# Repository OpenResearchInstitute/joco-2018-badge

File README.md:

# joco-2018-badge

Code and documentation for the unofficial electronic badge for the JoCo Cruise 2018.

This is based on the excellent work that the AND!XOR team produced for the DEFCON 25 Bender Badge.

All code and hardware design files are closed until Feb 26th, 2018 and then are licensed under the Apache license 2.0 unless superceded by notices in individual files or directories.

## Getting Started

Some resources must be installed outside of this source tree. One of these is the Nordic SDK.

Choose a place to install these on your file system. For example, we'll use "/src/joco-support/".

Download the version 12.3 of the Nordic SDK [from here](https://developer.nordicsemi.com/nRF5_SDK/nRF5_SDK_v12.x.x/nRF5_SDK_12.3.0_d7731ad.zip) and unzip it into the directory you chose.

It's known that later versions of the SDK are not compatible with the existing badge code. We may work on fixing that, which is why we don't install the SDK in the source tree for the project.

Now edit your shell init or rc file to set the following environment variable when you create a shell, substituting your chosen path:

```
export SDK_ROOT=/src/joco-support/nRF5_SDK_12.3.0_d7731ad
```

### Ubuntu Installation (non-ARM host)

Download the GNU ARM Embedded Toolchain. Choose one of these methods:

* Download the latest from <https://developer.arm.com/open-source/gnu-toolchain/gnu-rm/downloads> and unpack it into its own directory in `/usr/local`. Or,

* Download the version that Nordic used to test their SDK, 4.9 2015q3, from <https://launchpad.net/gcc-arm-embedded/+milestone/4.9-2015-q3-update> and unpack it into its own directory in `/usr/local`. Or,

* `sudo apt-get install gcc-arm-none-eabi` and take your chances on whatever version is current for your Linux. This may be your only option if you're running Linux on a non-x86 platform.

Then edit `$SDK_ROOT/components/toolchain/gcc/Makefile.posix` and change the value for `GNU_INSTALL_ROOT` to the directory where your toolchain was installed.

If you plan to hook up hardware for programming and debugging, you'll need the Segger JLink software. It's available from <https://www.segger.com/downloads/jlink/> for a variety of host platforms. We used version V6.18b, but the latest version is probably fine. To install on Ubuntu on an Intel PC:

`sudo dpkg -i <path-to-downloads>/JLink_Linux_V618b_x86_64.deb`

You'll also need a couple of command line tools from Nordic. These are available from <http://infocenter.nordicsemi.com/topic/com.nordic.infocenter.tools/dita/tools/nrf5x_command_line_tools/nrf5x_installation.html?cp=5_1_1>. We used version 9.7.0, but the latest version is probably fine. Install them in a location outside this project, like the Nordic SDK. For example using the location "/src/joco-support", you can do the following:

```
mkdir -p /src/joco-support/bin
cd /src/joco-support/bin
tar xvf <path-to-downloads>/nRF5x-Command-Line-Tools_9_7_0_Linux-x86_64.tar
```

Now edit your shell init or rc file to set the following environment variable when you create a shell, substituting your chosen path:

```
export NRFJ_BIN=/src/joco-support/bin
```

#### Ubuntu on an ARM Host

If you want to develop on an ARM-based host, most of the components are available.

The Nordic SDK is the same.

You should be able to `sudo apt-get install gcc-arm-none-eabi` to get the toolchain.

You can get JLink software [from Segger here](https://www.segger.com/downloads/jlink/#J-LinkSoftwareAndDocumentationPack)

The command line tools nrfjprog and mergehex are not currently available for ARM hosts. You can use the JLink tools to program the device, so you can probably work around nrfjprog.

### Build the code

`cd firmware/manbearpig`

`make`

`cd ..`

`./update.sh`

### JTAG interface hardware

To flash the code to the badge and use the Ozone debugger, you'll need a JTAG hardware interface.
The one that was used by the development team is the Segger [J-Link EDU Mini](https://www.segger.com/products/debug-probes/j-link/models/j-link-edu-mini/).

It's much easier to connect to the board if you use a short flat cable and a mating header on the board end. All these can be purchased from these retailers:

* [J-Link EDU Min from Adafruit](https://www.adafruit.com/product/3571)
* [Ten pin JTAG cable from Adafruit](https://www.adafruit.com/product/1675) (not the same as the one that comes with the debugger)
* [Header from Mouser](https://www.mouser.com/ProductDetail/Harwin/M50-3500542?qs=9fQaSFfsqsyXI0P9tFOVoQ%3D%3D)

### Flashing the target

Two ways, either:

`cd firmware`

`./provision.sh`

or

`cd firmware/manbearpig`

`make flash_softdevice`

`make flash`

The `make flash_softdevice` can be omitted after the first time.

### Setting up the Segger Ozone debugger

This was correct for Ubuntu 14.04.5 64 bit

Install the Ozone package [from here](https://www.segger.com/downloads/jlink/#Ozone)

The manual is useful (same link)

IMPORTANT NOTE: 

Ozone version 2.56 would not work for me. It would halt execution in seemingly random places and not load source code.

Version 2.54b works fine

If you're using the Segger edu device, Select the device as Nordic nRF52832_xxAA

Choose SWD for the debugger device and NOT USB.

open the badge .out file to bring in source files

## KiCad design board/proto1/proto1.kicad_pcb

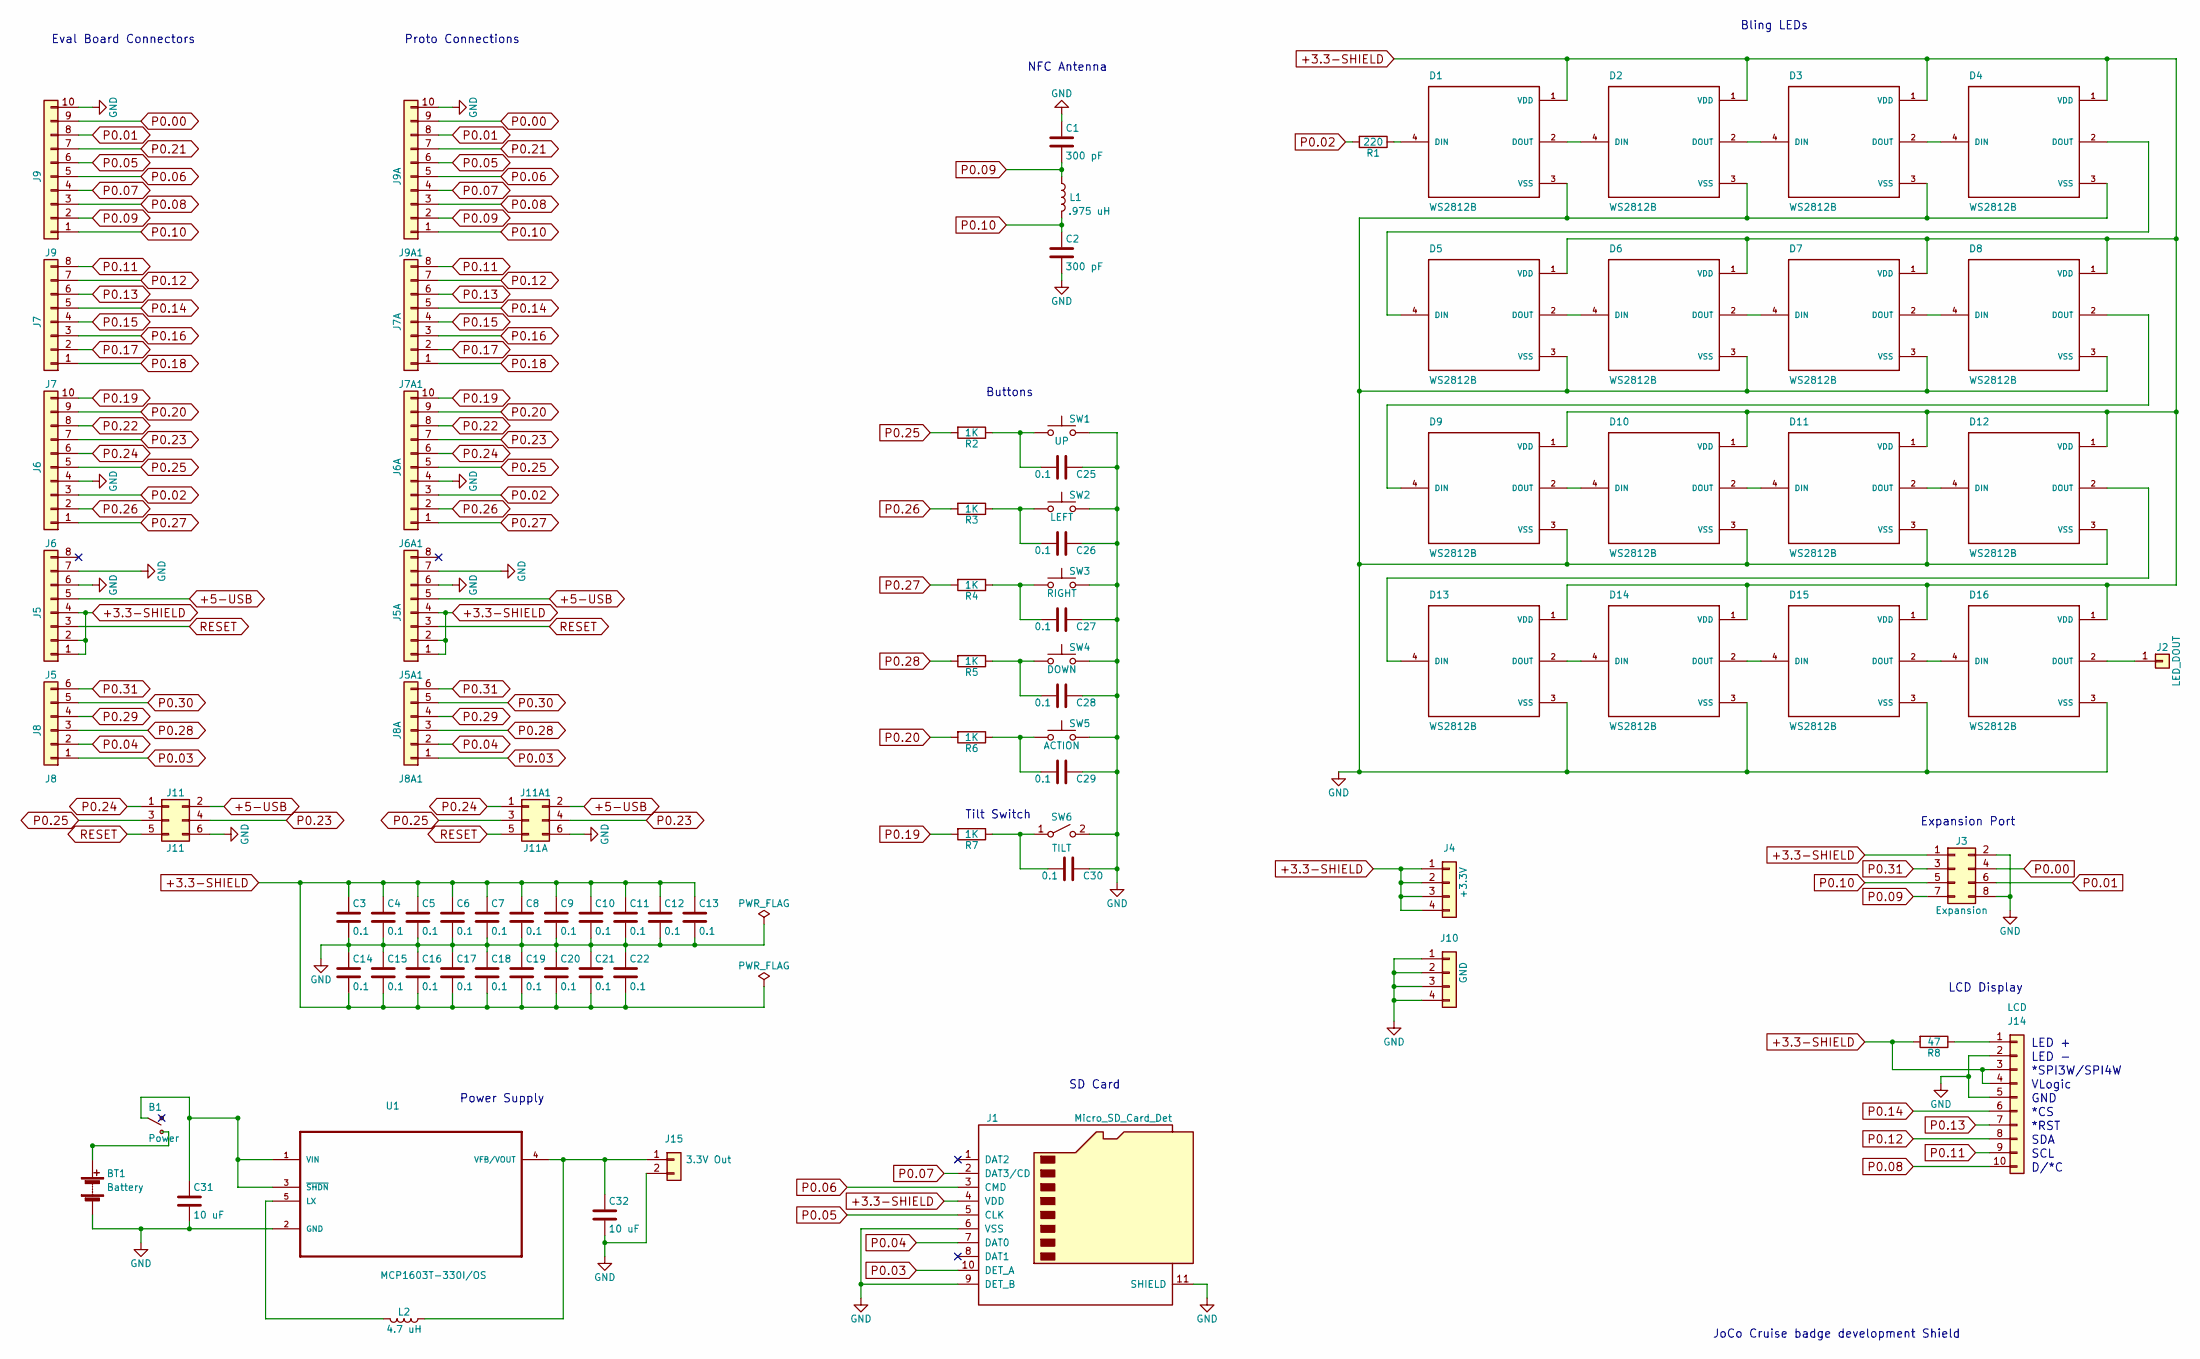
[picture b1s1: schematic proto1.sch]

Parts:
B1: Power; SSSS810701
BT1: Battery; R_Axial_DIN0411_L9.9mm_D3.6mm_P12.70mm_Horizontal
C1, C2: 300 pF; C_0805
C3, C4, C5, C6, C7, C8, C9, C10, C11, C12, C13, C14, C15, C16, C17, C18, C19, C20, C21, C22, C25, C26, C27, C28, C29, C30: 0.1; C_0805
C31, C32: 10 uF; C_1206
D1, D2, D3, D4, D5, D6, D7, D8, D9, D10, D11, D12, D13, D14, D15, D16: WS2812B; LED_WS2812B
J1: Micro_SD_Card_Det; newsdcard
J2: LED_DOUT; Pin_Header_Straight_1x01_Pitch2.54mm
J3: Expansion; Pin_Header_Straight_2x04_Pitch2.54mm
J4: +3.3V; Pin_Header_Straight_1x04_Pitch2.54mm
J5: J5; Pin_Header_Straight_1x08_Pitch2.54mm
J5A1: J5A; Pin_Header_Straight_1x08_Pitch2.54mm
J6: J6; Pin_Header_Straight_1x10_Pitch2.54mm
J6A1: J6A; Pin_Header_Straight_1x10_Pitch2.54mm
J7: J7; Pin_Header_Straight_1x08_Pitch2.54mm
J7A1: J7A; Pin_Header_Straight_1x08_Pitch2.54mm
J8: J8; Pin_Header_Straight_1x06_Pitch2.54mm
J8A1: J8A; Pin_Header_Straight_1x06_Pitch2.54mm
J9: J9; Pin_Header_Straight_1x10_Pitch2.54mm
J9A1: J9A; Pin_Header_Straight_1x10_Pitch2.54mm
J10: GND; Pin_Header_Straight_1x04_Pitch2.54mm
J11: J11; Pin_Header_Straight_2x03_Pitch2.54mm
J11A1: J11A; Pin_Header_Straight_2x03_Pitch2.54mm
J14: LCD; ZIF-505110-1092
J15: 3.3V Out; Pin_Header_Straight_1x02_Pitch2.54mm
L1: .975 uH; nfc-test2
L2: 4.7 uH; MAMK2520
R1: 220; R_0805
R2, R3, R4, R5, R6, R7: 1K; R_0805
R8: 47; R_0805
SW1: UP; PTS810
SW2: LEFT; PTS810
SW3: RIGHT; PTS810
SW4: DOWN; PTS810
SW5: ACTION; PTS810
SW6: TILT; R_Axial_DIN0207_L6.3mm_D2.5mm_P15.24mm_Horizontal
U1: MCP1603T-330I/OS; SOT95P280X110-5N

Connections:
+3.3-SHIELD: C3.1, C4.1, C5.1, C6.1, C7.1, C8.1, C9.1, C10.1, C11.1, C12.1, C13.1, C14.2, C15.2, C16.2, C17.2, C18.2, C19.2, C20.2, C21.2, C22.2, D1.1 (VDD), D2.1 (VDD), D3.1 (VDD), D4.1 (VDD), D5.1 (VDD), D6.1 (VDD), D7.1 (VDD), D8.1 (VDD), D9.1 (VDD), D10.1 (VDD), D11.1 (VDD), D12.1 (VDD), D13.1 (VDD), D14.1 (VDD), D15.1 (VDD), D16.1 (VDD), J1.4 (VDD), J3.1, J4.1, J4.2, J4.3, J4.4, J5.1, J5.2, J5.4, J5A1.1, J5A1.2, J5A1.4, J14.3, J14.4, R8.2
+5-USB: J5.5, J5A1.5, J11.2, J11A1.2
GND: BT1.2 (-), C1.1, C2.2, C3.2, C4.2, C5.2, C6.2, C7.2, C8.2, C9.2, C10.2, C11.2, C12.2, C13.2, C14.1, C15.1, C16.1, C17.1, C18.1, C19.1, C20.1, C21.1, C22.1, C25.1, C26.1, C27.1, C28.1, C29.1, C30.1, C31.2, C32.2, D1.3 (VSS), D2.3 (VSS), D3.3 (VSS), D4.3 (VSS), D5.3 (VSS), D6.3 (VSS), D7.3 (VSS), D8.3 (VSS), D9.3 (VSS), D10.3 (VSS), D11.3 (VSS), D12.3 (VSS), D13.3 (VSS), D14.3 (VSS), D15.3 (VSS), D16.3 (VSS), J1.6 (VSS), J1.9 (DET_B), J1.11 (SHIELD), J3.2, J3.8, J5.6, J5.7, J5A1.6, J5A1.7, J6.4, J6A1.4, J9.10, J9A1.10, J10.1, J10.2, J10.3, J10.4, J11.6, J11A1.6, J14.2, J14.5, J15.2, SW1.2, SW2.2, SW3.2, SW4.2, SW5.2, SW6.2 (B), U1.2 (GND)
unnamed: B1.1 (B), BT1.1 (+)
unnamed: B1.2 (COM), C31.1, U1.1 (VIN), U1.3 (~SHDN)
unnamed: C25.2, R2.1, SW1.1
unnamed: C26.2, R3.1, SW2.1
unnamed: C27.2, R4.1, SW3.1
unnamed: C28.2, R5.1, SW4.1
unnamed: C29.2, R6.1, SW5.1
unnamed: C30.2, R7.1, SW6.1 (A)
unnamed: C32.1, J15.1, L2.1, U1.4 (VFB/VOUT)
unnamed: D1.2 (DOUT), D2.4 (DIN)
unnamed: D1.4 (DIN), R1.1
unnamed: D2.2 (DOUT), D3.4 (DIN)
unnamed: D3.2 (DOUT), D4.4 (DIN)
unnamed: D4.2 (DOUT), D5.4 (DIN)
unnamed: D5.2 (DOUT), D6.4 (DIN)
unnamed: D6.2 (DOUT), D7.4 (DIN)
unnamed: D7.2 (DOUT), D8.4 (DIN)
unnamed: D8.2 (DOUT), D9.4 (DIN)
unnamed: D10.2 (DOUT), D11.4 (DIN)
unnamed: D9.2 (DOUT), D10.4 (DIN)
unnamed: D11.2 (DOUT), D12.4 (DIN)
unnamed: D12.2 (DOUT), D13.4 (DIN)
unnamed: D13.2 (DOUT), D14.4 (DIN)
unnamed: D14.2 (DOUT), D15.4 (DIN)
unnamed: D15.2 (DOUT), D16.4 (DIN)
unnamed: D16.2 (DOUT), J2.1
unnamed: J14.1, R8.1
unnamed: L2.2, U1.5 (LX)
P0.00: J3.4, J9.9, J9A1.9
P0.01: J3.6, J9.8, J9A1.8
P0.02: J6.3, J6A1.3, R1.2
P0.03: J1.10 (DET_A), J8.1, J8A1.1
P0.04: J1.7 (DAT0), J8.2, J8A1.2
P0.05: J1.5 (CLK), J9.6, J9A1.6
P0.06: J1.3 (CMD), J9.5, J9A1.5
P0.07: J1.2 (DAT3/CD), J9.4, J9A1.4
P0.08: J9.3, J9A1.3, J14.10
P0.09: C1.2, J3.7, J9.2, J9A1.2, L1.1
P0.10: C2.1, J3.5, J9.1, J9A1.1, L1.2
P0.11: J7.8, J7A1.8, J14.9
P0.12: J7.7, J7A1.7, J14.8
P0.13: J7.6, J7A1.6, J14.7
P0.14: J7.5, J7A1.5, J14.6
P0.15: J7.4, J7A1.4
P0.16: J7.3, J7A1.3
P0.17: J7.2, J7A1.2
P0.18: J7.1, J7A1.1
P0.19: J6.10, J6A1.10, R7.2
P0.20: J6.9, J6A1.9, R6.2
P0.21: J9.7, J9A1.7
P0.22: J6.8, J6A1.8
P0.23: J6.7, J6A1.7, J11.4, J11A1.4
P0.24: J6.6, J6A1.6, J11.1, J11A1.1
P0.25: J6.5, J6A1.5, J11.3, J11A1.3, R2.2
P0.26: J6.2, J6A1.2, R3.2
P0.27: J6.1, J6A1.1, R4.2
P0.28: J8.3, J8A1.3, R5.2
P0.29: J8.4, J8A1.4
P0.30: J8.5, J8A1.5
P0.31: J3.3, J8.6, J8A1.6
RESET: J5.3, J5A1.3, J11.5, J11A1.5

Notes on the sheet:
Eval Board Connectors
Proto Connections
NFC Antenna
SD Card
Bling LEDs
Buttons
Power Supply
Tilt Switch
LED +
LED -
*SPI3W/SPI4W
VLogic
GND
*CS
*RST
SDA
SCL
D/*C
LCD Display
JoCo Cruise badge development Shield
Expansion Port

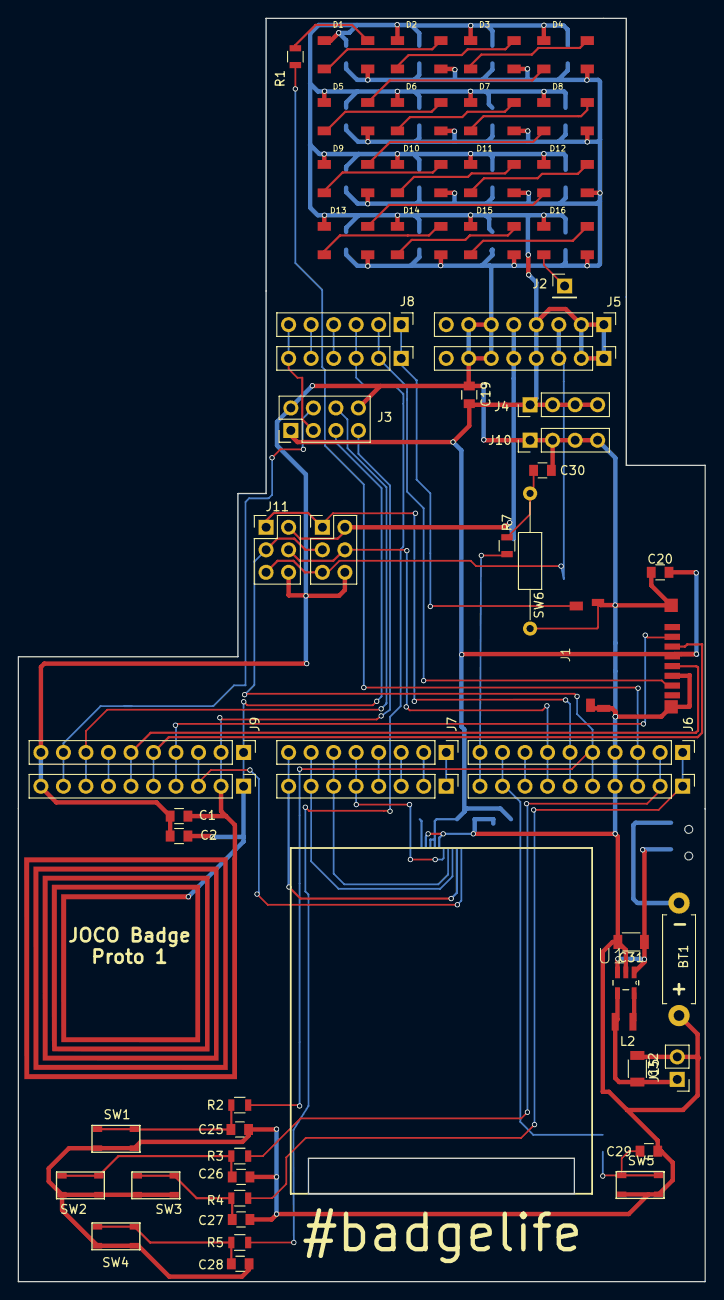
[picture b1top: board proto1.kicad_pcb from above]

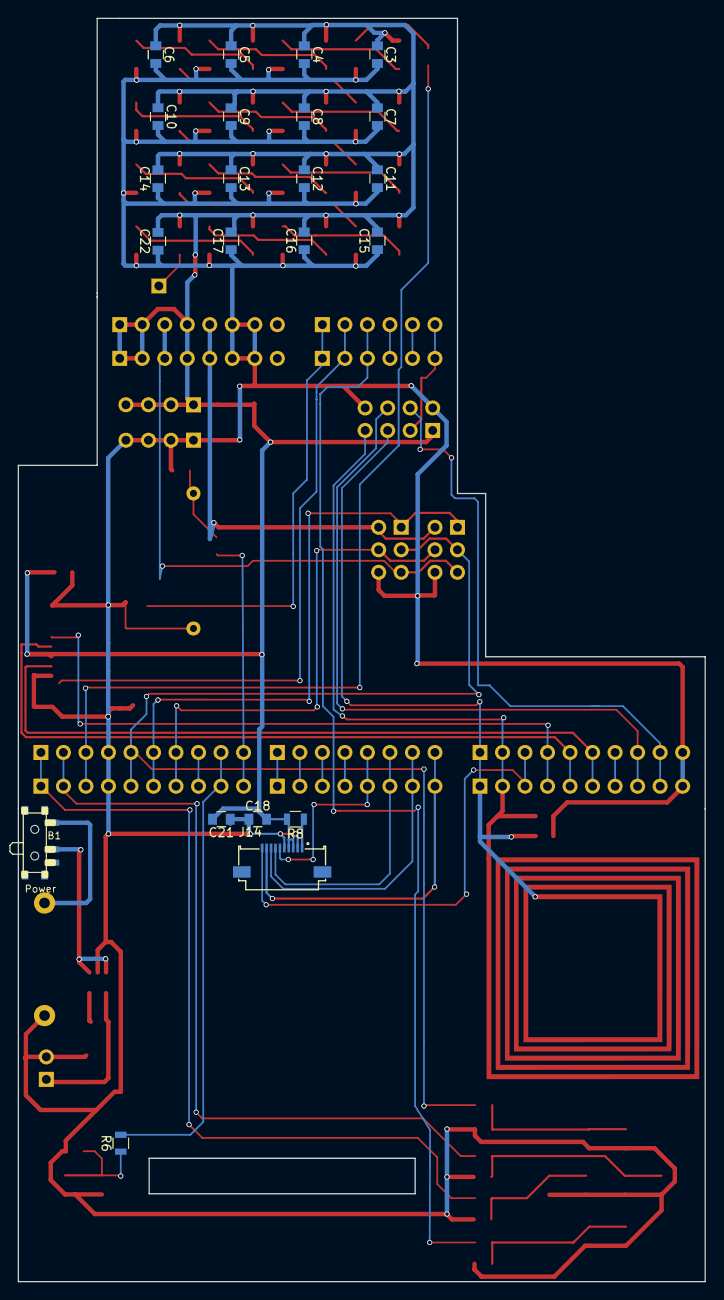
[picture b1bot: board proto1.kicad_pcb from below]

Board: 2 copper layers, 77.5 x 142.5 mm, 84 parts (22 on the bottom side), 64 nets.

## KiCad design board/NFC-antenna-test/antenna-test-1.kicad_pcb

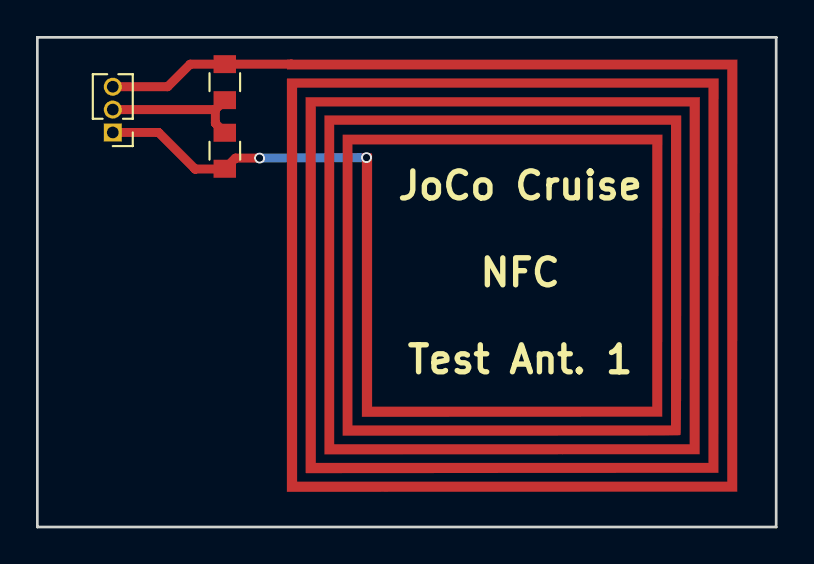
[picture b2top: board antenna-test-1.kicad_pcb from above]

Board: 2 copper layers, 41.0 x 27.2 mm, 4 parts (0 on the bottom side), 3 nets.

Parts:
C1, C2: C; C_0805
J1: ANT; Pin_Header_Straight_1x03_Pitch1.27mm
L1: L; nfc-test2

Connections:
GND: C1.1, C2.2, J1.2
unnamed: C1.2, J1.3, L1.1
unnamed: C2.1, J1.1, L1.2

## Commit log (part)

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2017-08-10 readme
2017-08-10 initial commit of ANDnXOR bender source
2017-08-14 Ignore a warning and clean up whitespace
    gcc is throwing a warning for using char as an array subscript even though the declaration is for uint8_t. So ignore that.
    Also, clean up lots of extra spaces and make tab use consistent
2017-08-20 Move spreadsheet to google docs, and update README
2017-08-27 Add first unfinished proto board designs
2017-08-31 more layout work
2017-08-31 unignore and add library files fro kicad
2017-09-04 lots more layout work
2017-09-05 Add rescue lib from version change
2017-09-05 Add cache.lib
2017-09-06 layout maybe finished
2017-09-12 Add final board info for proto1
2017-09-16 coverting files to Eagle, checking in data sheets
2017-09-16 added power suppy to proto2
2017-09-21 adding additional parts
2017-09-21 adding bling LEDs to proto2
2017-10-01 Remove Nordic SDK from the repo, add instructions.
    In order to make it cleaner to switch versions of the SDK,
    we no longer check the SDK into the repository.
    In order to make it easier to get started with the toolchain,
    there are now detailed instructions in README.md.
2017-10-01 Remove Nordic Command Line Tools from repo.
2017-10-01 Improve getting started instructions.
2017-10-04 Typo in SDK URL
2017-10-04 Improved Getting Started info
2017-10-06 strip out botnet code
2017-10-07 Move the SDK and platform-specific tools out of the repo
    Place the Nordic programming tools and SDK outside the git repository and use environment variables to point to them.
    This prevents having to maintain files in the local directory tree which aren't under git.
2017-10-11 Find Makefile.posix in the new location
2017-10-27 Change some defcon text to joco
2017-10-27 Make button repeat delay longer during code entry
2017-10-31 Add support for NFC
2017-11-12 adding outline of monkey to PCB
2017-11-12 silkscreen for monkey
2017-11-12 added gold teeth
2017-11-12 guides for LEDs, etc
2017-11-12 add guides for LEDs; place LEDs, battery, CPU
2017-11-12 adding original AI from Amy; board specifications (TBD)
2017-11-12 add .DS_Store to gitignore
2017-12-02 copy Amy's board revision to proto2 (change tPlace artwork)
2017-12-02 reduce LEDs to 14, add tilt switch, draw NFC antenna
2017-12-02 added expansion connector to schematic
2017-12-02 added programming cable connector
2017-12-02 add decoupling caps
2017-12-02 layout in process
2017-12-03 lots of routing going on
2017-12-03 routing almost done. I hate 2-layer PCBs
2017-12-03 goffing around with artwork
2017-12-03 change to SW-200D part
2017-12-03 remove unneeded pin labels
2017-12-04 added lanyard holes; thanks to AND\!XOR
2017-12-04 add earring holes
2017-12-05 changes for errors found by AI4QR
2017-12-16 remove Old backer bling code from firmware and files from SD card
2017-12-18 final changes to proto2, saving Gerbers
2017-12-27 Shuffle boot image and ANDNXOR backer bling
2017-12-27 change LED indices and function names for pirate monkey
2017-12-27 remove whiskey pirate clue for DC25 from the pirate bling
2017-12-27 Change various ANDnXOR menu headers and other things to JOCO2018
2017-12-28 Fix SD card omissions
2017-12-28 Fix some broken menus
2017-12-28 remove unused Bender archive from SD Card
2017-12-28 Fix LED bling for andnxor backer bling
2017-12-29 Change company ID for joco badge, update to handle interactions with bender
2017-12-29 increase menu delay to prevent double buttons
2017-12-29 Add image file tools
2017-12-29 Add Wil Wheaton bling mode
2017-12-29 Add pirate monkey boot intro image
2017-12-29 Add the readme from andnxor for the SD card
2018-01-01 move resistor out of way of display
2018-01-01 reset masks to 4mil
2018-01-01 add secret resistor
2018-01-07 remove andnxor reference and add a way to enable all bling modes easily
2018-01-07 Fix a typo in airplane mode
2018-01-07 Make tooth LED gold and flashing
2018-01-07 Change the background image for the menus to a pirate monkey one
2018-01-07 remove the ANDNXOR chip8 game
2018-01-08 move flex connector 1mm to the North
2018-01-08 move expansion connector
2018-01-08 move team and thanks position due to tild switch nove to back of board
2018-01-08 rotated SD card 180-degrees
2018-01-08 update assembly instructions for PCB
2018-01-09 change lanyard holes to 4mm
2018-01-10 WIP schematic rules
2018-01-10 change mask to blue for 5 boards
2018-01-10 swap out switch for one with better mechanical stability
2018-01-10 production board and Gerbers
2018-01-10 make note about hole in center of PCB
2018-01-20 Cropped GIFs for Bling
2018-01-20 Move new images to a new directory for source images
2018-01-20 Add more source image files
2018-01-20 Change yet anothe rbender string to joco, this time in ble
2018-01-21 Add code reading notes.
    These are notes I took while reading the AND!XOR Bender badge code,
    concentrating on particular subjects. They may or may not be useful
    for others trying to understand the code.
2018-01-21 Checked in DC25 Wall of Bender code to start Wall of Joco
2018-01-22 Add new bling modes
    Added new files to the SD card, bumped SD version
    Added new bling to the menu
    Deleted old files from SD card
2018-01-22 Resolve stack/heap crash in menu system
    Changed the menu system to cache only the icons that are visible
    on screen, instead of every icon for every menu entry. This relaxes
    the limit on how many menu items there can be, so specifically the
    custom bling menu can be much longer.
    Also installed the mechanism to control the sizes of the stack and
    the heap, in config/startup_config.h. However, the sizes currently
2018-01-26 Add for NFC payload
    Add actual content for the NFC tag emulation, consisting of a fixed text string.
2018-01-27 Update Wall of JoCo README for RTC.
2018-01-27 Update Wall of JoCo README, remove DEFCON
2018-01-27 Change the unlock constants and remap to bling for joco
    Edit the #define mask names to match what we're using them for in joco. Comment out some of the code that's used in beacon receiving to enable these, because we need to move it to be based on badge p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
2018-01-28 Add initial joco gameplay files
    Add new files and constants for game play. Add the score and last_level_dispensed to the state that gets saved.
2018-01-28 put some reasonable numbers in for RSSI
2018-01-28 Put the JoCo data we need in the BLE advertising data
    The 'level' field was repurposed to lld (last_level_dispensed)
    The 8 bit avatar field was replaces with a 16 bit score field.
    Data offsets were adjusted accordingly in the data.
    The new fields are read into the badge_db information for badges that are 'heard'
    This has not yet been tested to make sure it's sent and received correctly.
2018-01-29 Remove the rest of the badge activation code and tests
2018-01-29 change state encryption key
2018-01-30 Add code reading notes for connected mode.
2018-01-31 Merge trinket dispensing flag with score in BLE advertising
    It turns out that there was not enough room in the BLE data to add one more byte of data. By doing this, if the name is a full 8 bytes long, then it gets translated into a short naem format, and we d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
    The solution is to simply adevrtise a flag that incicates that the badge has some outstanding 'credits' for trinkets which can be dispensed. This flag is the high but of the 16 bit unsigned score val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
2018-02-01 Replace 6 calls to snprintf
    It seemed dumb to call snprintf 6 times to convert a byte array to Ascii hex, and the terminating numm that is created was wrong, so include a small function to do this task.
2018-02-01 Update BLE score on load from SD card
2018-02-01 Add basic BLE service for score and lld.
    Created a GATT service with two characteristics. One is a read-only
    struct containing the current score and last_level_dispensed. The
    other is a write-only 64-bit command code, which currently implements
    commands to set score and lld.
    Security: none yet. The read characteristic is completely public, and
    once that's spoofed it's easy to trick the station into sending you
2018-02-03 Added File Crypto Notes to codereading
2018-02-04 add db functions to store badges we've contacted/visited
2018-02-04 Make a copy to encrypt before encrypting!
2018-02-08 Crypto state and score cleanup
    Added macros in util_crypto.h to encapsulate some of the procedure for
    accessing the util_crypto routines. Changed mbp_state.c and score_ble.c
    to use them.
    Switched from separate score_set and lld_set functions to a single
    score_update function that does its own fetching of the data from the
    mbp_state database. Changed mbp_state.c to use it. The new update
2018-02-09 Add new visit tracking
    Completely rework the db/list of heard badges.
    Only joco badges that we haven't 'visited' are stored in
    the primary active list. Other badges and one's we've
    visited are stored in a second cache list, which is backed
    by the database on SD card for vistied badges.
2018-02-09 Change Scoring and joco hello bling
2018-02-10 Add a file to the DB directory so git keeps the directory
2018-02-11 Add name to NFC data
2018-02-11 Add a menu selection to view current game status
2018-02-11 Fix hello timing
    Hello timer was set using the non-local millis, and the next hello time
    was set to zero, which resulted in immediate hellos on boot before the
    splash screen even finished. Fixed this.
2018-02-11 Darker background image for joco hello bling
2018-02-11 remove some char cast warnings
2018-02-12 Add eye animation in idle mode
2018-02-13 Update NFC tag data on name change
2018-02-13 Truncate NFC data length to only used bytes
2018-02-13 Change icon for menu score entry and other improvements
    Also exit the score display on any button press.
    Bumped SD card and software version numbers.
2018-02-13 Score bling now displays the name of the otehr badge scored
2018-02-13 Reverse order of score and bling menu items
2018-02-13 Make top level game over animation loop
2018-02-14 Change global time secret so we don't take updates from Bender badges
2018-02-14 Add scoring for playing chip8 games
2018-02-14 remove chip8 demos
2018-02-14 Add name to seen list data
2018-02-14 Display nearby badges from both active and seen lists
2018-02-14 Update license text in firmware files
2018-02-14 clean up cruft in comments
2018-02-14 Fix calculation of outstanding trinkets
2018-02-15 Add Device ID to NFC packet
2018-02-15 Fix "trinkets avail" on score screen
2018-02-15 require more signal strength to score a visit
2018-02-15 Move test for seekrit jumper earlier in boot
2018-02-16 replace a couple of preview images with a black display
2018-02-16 Add some notation to the TCL README
2018-02-16 Remove unused botnet files from SD card
2018-02-16 Change README for twitter
2018-02-16 display nearby count in test screen
2018-02-16 Change the LED indices for the TCL eyes demo
2018-02-16 bump SD version for Joco copy run
2018-02-16 Fix BLE bug and kludge LLD update
2018-02-16 Version to 1.8
2018-02-16 Make score characteristic stay in user memory
2018-02-16 Update advertised LLD when trinket is dispensed
2018-02-16 Spell it "Airplne Mode" to fit on the screen
2018-02-17 Unlock all master bling for any master
2018-02-17 put Wil Wheaton bling behind a password
2018-02-17 Version and build for release
2018-02-18 fix script
2018-02-28 Add NFC reader README
2018-02-28 Add pdf of schematic
2018-03-05 Add proto1 schematic pdf
2018-04-24 Add BOM to board info
2018-04-24 Add debugger info to README
2018-04-24 Add more documentation of interest to developers
2018-04-24 fixup markdown
